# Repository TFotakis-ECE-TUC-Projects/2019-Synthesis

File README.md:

# TUC Course: Analysis and Design (Synthesis) of Telecommunication Systems
## Project: Distributed Smoke Detection using Lasers

### Development Team Members
Andrianakis Manos
Fotakis Tzanis
Giannakopoulos Orestis
Kotridis Giorgos
Neonakis Paulos
Nichoritis Thanos
Ouroutzoglou Michail
Piskopos Dionisis
Polyzos Christos
Topalis Thanasis

### Professor Assistants
Giannelos Vaggelis
Vougioukas Giorgos

## Supervisor Professor
Bletsas Aggelos

# Introduction
---

## Semester Project Overview
The purpose of this project is to create a wireless sensor network in order to detect smoke in the TUC ECE's department building canteen and pinpoint its source.

### Main idea
Smoke has the ability to diffuse and absorb light, thus, by utilizing cheap sensors such as photodiodes, phototransistors or even photovoltaic panels, the impinging light’s intensity can be tracked and from its waveform in respect to time the existence of smoke can be inferred.
In order to cover a large amount of the available plane, lasers can be used in combination with mirrors as shown in Fig.1. By dividing the plane into cells/tables of 2 rows and 3 columns (see Fig.1), detection of smoke in a specific cell/table can be done by combining data from multiple sensors (e.g., row-1 and column-2 could detect smoke from table-2). 

### Project Structure
Work was split into 3 working groups, Hardware, Middleware and Software, in order to divide the workload among the project members. 
The system includes five sensor nodes (slaves, depicted in Fig.2-right), one base node (master, depicted in Fig.3) and one server PC (laptop, depicted in Fig.4). 
    • Slave: Controls laser diode, measures laser intensity and sends the measurement to the master node.
    • Master: Gives instructions to slave nodes so that they get synchronized to make the laser intensity measurements and to report them back on specific time slots. After the collection of all the measurements, a message to the server is sent with the collected data.
    • Server: Collects measured data, runs the detection algorithm on the collected data and updates the website.

Figure 1: Initial idea. Top view.

Figure 2: Slave Node on the left, mirror on the right.

Figure 3: Master Node.

Figure 4: Server on a laptop on the left, Server on a Raspberry Pi Zero W on the right.

Figure 5: Fully connected System.

### Technical Difficulties
Due to environmental difficulties (walls prone to machinery vibrations, mounting issues, etc) that will be discussed below, time limitations became significant to the project’s overall development. As a result, the initial goal of detecting smoke on a grid was transformed into detecting smoke on a serial basis.

# Implementation
---

## Hardware

In this section we shall describe the analog part of our system. 

First of all, we shall analyze the basic hardware, as well as the installation components, that compose the system’s slave nodes.
Components:
    • Diode Laser (red)
    • Photovoltaic Panel
    • Power Supply
    • Mirror reflectors
    • Switching circuit
    • Optical filter
    • Control Unit & Radio
    • Case
    • Mounting Materials

### Diode Laser
For the purpose of our project, Diode Lasers (red) were the most power efficient and low cost. Additionally, red light has the biggest wavelength (compared with green and blue) thus, it is the least harmful for the human eye.

### Photovoltaic Panel
The photovoltaic panel is connected to the ADC (Analog to Digital Converter) of the Daughter Card in order to digitalize the signal.
Power Supply
The power supply was a major and very challenging problem we had to solve. Our first approach was to use conventional batteries. However, this approach did not provide a strictly constant DC voltage as long as the batteries were quickly discharged. So we had to make a regulator circuit to overcome this problem. Instead of this we used power banks, which were low cost, efficient, rechargeable and provided the desired DC constant power supply.
Mirror reflectors
Used to redirect the light beam to the desired destination.

### Switching Circuit

Figure 6: Laser amplifier circuit.

This circuit was used for duty-cycle purposes, in the interest of minimizing the power consumption of the project. For the implementation of the switching circuit we used the following components:
    • 10 kΩ resistance
    • 2N3904 transistor
The switch circuit is represented in Fig. 6. In order to use the transistor as a switch circuit, we connected a 3,3 V output provided by the used target board via a resistance to the Base of the transistor, while connecting the output of the transistor (Collector) to the negative polarity of the diode laser. As a result, we manage a power consumption approximately to 100 mW for each laser circuit contained in a grid.

### Optical filter
In order to eliminate the ambient light’s intensity inside the slave’s case and only let the laser pass through, optical filters were used. An optical filter is a semi-transparent material that absorbs specific light wavelengths. The ones used in this project were filters that only allowed red pass through, which is the color of the used lasers. Such a filter could be purchased as a sheet of paper. However, for the purposes of this project and because of time shortage, several layers of red colored transparent tape were used in the place of the optical filter. Although, an optical filter cannot cut off the whole ambient light (ambient light also includes red wavelengths) and at the same time let the red laser pass through, it was a good enough solution, cutting off most of the other wavelengths.

### Control Unit & Radio
The slave node’s Control Unit & Radio is comprised of a Silicon Labs C8051F321 Daughter-Card, an 8-bit microcontroller mounted on a small development board with various IO ports (Buttons, IO pins, MicroUSB connector, etc), and a Silicon Labs CC2500 Radio Shield, which is an 8-bit microcontroller with radio modulation capabilities and I2C communication. It is responsible for collecting the needed measurements through its ADC (Analog to Digital Converter) component (see Middleware section), processing them and sending them to the master node and, also, switching its laser’s state for maintaining the system’s low power consumption characteristics.

### Case
Second handed Electrical Junction Boxes were used to accommodate all slave’s components. Two holes were drilled on its front face, one for holding the laser diode and one for letting the laser beam enter the box and hit the photovoltaic panel. The photovoltaic panel was placed as far from the hole as possible in order to eliminate the ambient light hitting it for reasons that will be discussed in the middleware section. For further elimination, the aforementioned optical filter was placed on top of that hole.

### Mounting Materials
Mounting hardware not only inside the slave’s case but also on the walls without establishing permanent installations (e.g. using holes and/or screws) that could damage the building, was a difficult, time and resource consuming task. Solutions such as 3D printed bases were tested in combination with materials such as Blu Tack and double sided tapes. Despite their light weight, stability problems surfaced. Therefore, the lasers' beams were diverted from the target. At last, the slaves cases were mounted on the walls using double sided tape and the reflection mirrors using only Blu Tack, which helped to easily redirect the laser beams.

### Slave Node Overview
Fig. 7 shows the wiring between the components we already discussed. Concerning the power supply of the circuit we used the daughter-card’s pins to provide power for both the circuit and the positive polarity of the laser diode. The daughter-card feeds the laser positive polarity and the switching circuit’s enable signal with VCC = 3.3V. Finally, the daughter-card’s power was provided by a 5V, 2600 mAh power bank which, in paper, could last for more than 18-hours of continuous use.

Figure 7: Inside a slave’s casing.

### Master Node Overview
The base station/master node is comprised of a Silicon Labs C8051F320 DevKit, an 8-bit microcontroller mounted on a development board with various IO ports (Buttons, IO pins, DB9 connector, power supply connector, etc), a Silicon Labs CC2500 Radio Shield, an 8-bit microcontroller with radio modulation capabilities and I2C communication, a 5V power adapter and a Serial to USB adapter. The master node exchanges data with all slave nodes via the aforementioned radio shield. The collected data is then forwarded to the server via the DevKit’s serial port (utilizing its UART capabilities), which is then adapted to a USB port through the Serial to USB adapter. The latter is needed because, at the time of writing this report, the serial port is being deprecated and obsolete from every modern PC and also the Laptop/Raspberry Pi was used as a server.

## Middleware

### Connecting The Devices
The main objective was to collect the voltage values from each of the five slaves to the master node in order to forward them to the software to be processed for the detection. Achieving a reliable communication between one slave and the master was the first aim. Afterwards, the master node’s code was adjusted in order to control the rest.
The implementation began by writing code for the exchange of simple packets between the master and the slaves. RF-related registers were fine-tuned with the aid of the smartRF studio 7, which is an application that takes as input the desired design parameters and returns code that configures the nodes’ radios accordingly.
Every device can be used in one of the two available modes, receiver mode and transmitter mode, at a time. Checking for good communication between devices, one was set in transmitter mode and the other in receiver mode. As soon as they exchanged a single packet they would both switch modes and begin a new packet exchange. This process of exchanging packets would continue until a packet was lost. This method is called ping pong because a single packet is sent from one device to another and back again, like a ball of ping pong. 

### Handling the Data
After a reliable communication between devices has been established, the next step was to measure voltage values given from a power supply using the daughter-card’s analog-in pins and converting them into bytes, which will be later sent to the master. For this procedure an ADC (analog to digital converter) is required, an electronic component inside the slave’s microcontroller, which by comparing a port’s voltage to a set reference voltage, returns a measurement from 0 to 1023 of how close the port’s voltage is to the reference’s voltage. This method is called analog to digital conversion, because it accepts an analog, continuous signal and converts it into a discrete number referring to a specific moment of time. Following the addition of the appropriate functionality for the ADC part, the results of the converter were put in the tx Buffer (the buffer where the values that we want to be sent are into) in order to be transmitted to the master. After receiving the values from the slave, it was needed to view if the values from the power supply were sent correctly and in order to the master. Functionality extension had be made on the master, so that serial port communication capabilities could be used via the UART protocol. In order to view the received data from the PC, the Hercules application was used.

### Communication protocol
According to the initial plan, the master node was supposed to send a request to the first slave, waiting to receive a measurement, and then proceed to the next. After the implementation of this protocol, we came to the conclusion that this was not the ideal method as the whole procedure took around 2.5 seconds (500ms for each slave). This period was way too big for a smoke detection task, so a new, faster protocol had to be designed.
The final communication protocol expects the master to broadcast to all slaves an instruction to take a measurement. After the needed period of time for a measurement to be made (approximately 200ms), the master, starting from the first slave, sends a packet to request for that measurement and when received it continues to the next one, until it has collected all slaves’ measurements. That method was proved to be fast enough for our implementation as the elapsed time is being reduced to around 500ms.
Although, another issue occurred, as in unpredicted time, the communication ended suddenly, because a transmitted packet was lost. In this case, the procedure crashed as the master waited forever for a packet to be received. For that reason, a timeout routine was created which leads to a timeout after a short, pre defined period of time of 100ms, in order to avoid system crashes. When a timeout occurs, master continues its execution and requests the next node’s measurement. As a result, even in the case that a slave node is being lost from the network (e.g. battery fully discharged, change in environment leading to poor network connection, etc), the system’s execution will continue with no impact, except for always sending the last received measurement of the lost node.

### Measurements
To get a sense of the photovoltaic’s behaviour under the ambient light and the selected laser beam, measurements were made using one of the lab’s oscilloscope. Because most of the ambient light was generated from fluorescent lamps, which their operating principle is charging mercury to emit ultraviolet light to the tube’s gas, which it then emits visible light, a frequency of around 100 Hz was detected. Trying to remove that frequency, as well as, the ADC’s measurement noise, an average of 2048 measurements was computed, which was then sent to the master.
As soon as the first real world test took place at the desired area revealing the realistic measurements that had to be taken under consideration, a slight change in the measurement’s functionality had to be made in order to increase the sensitivity. The previous measurement method disadvantage was that it only measured ambient light’s intensity (which cannot be avoided) in combination with the laser’s intensity. However, the wanted measurement was (if possible) to measure only the laser’s intensity. So, to eliminate the ambient light’s intensity, it had to be measured and subtracted from the combination of ambient light and laser. The final measurement method works as follows: 
The laser is turned on, while the ADC takes 1024 measurements which are summed up to a variable, SUM, representing a measurement of the combination of the ambient light and the laser. Afterwards, the laser is turned off, while the ADC takes another 1024 measurements, which represent a measurement of the current ambient light. Those measurements are then subtracted from the SUM variable. Finally, the SUM is divided by 1024 to calculate the measurements’ arithmetic mean, which represent a close approximation of the laser’s intensity. To further eliminate ambient light’s intensity which caused the photovoltaic to operate on its nonlinear area, an optical filter, which only lets red (the laser’s color) to pass through, was used as discussed above.

### Master Node Algorithm Flow Chart

Figure 8

### Slave Node Algorithm Flow Chart

Figure 9

## Software
The software team was responsible for fetching the data from the master node, keeping a log of them, and plotting them on MATLAB-like environment for the user to overwatch. In addition to that, accurate real-time detection of smoke is offered through simple digital signal processing, as well as the ability to project this information on a website, reachable from throughout the campus, alongside (un)pleasant sound effects as a notification/warning for the end user.

### Website & Data Handling
The website’s backend was created using the DJango framework, a high level web framework for rapid development, clean and pragmatic design. As it uses Python, it was the most suitable for the project’s needs because the smoke detection algorithm could be easily implemented inside the backend’s features. Last but not least, the data collection from the master node is done using the UART protocol through the PC’s serial port. 
On server launch, a new thread is created with the purpose of reading the serial port and storing its data into a FIFO buffer, from which the detection algorithm could make the needed calculations. Whenever a new calculation is ready, it is stored in a variable which can be sent to all the website’s connected clients. This thread also logs the received data, the timestamp of each measurement and the result of the detection. This can be quite useful since it allows the user to examine events in the past, even if the system is left unsupervised.
Another thread is also spawned in order to plot the received waveforms of each sensor on the screen.
The reason why separate threads are needed is because some of the aforementioned functionalities are blocking, meaning that the server would not continue its execution if single threaded.
The website’s frontend was created using plain HTML5 and CSS3 for the user interface as well as jQuery for dynamically updating the states of the predefined measured areas. In more detail, when the website is accessed, a periodic routine is triggered every 8 second to request from the server the current areas’ states. A json response is returned from the backend containing the needed data, which are stored in the previously mentioned variable. 
Whenever smoke is detected in an area, the corresponding area on the website turns from green to red and a sound effect is played, in order to catch the attention of the users.

### Observations On Data
Several factors were considered before deciding what is a good way to approach the detection. 
The ambient light introduced bias on the sensors. Normally this wouldn’t pose a problem, however considering the day/night cycle as well as the lights turning on/off, this was a problem. In addition to that, if the smoke settled in the room, the ambient light as well as the laser rays would be affected by a slow, time-dependant factor (e.g., day/night transition, smoke clearing out). These effects are different on each sensor considering their different location in the room and their electronic characteristics (e.g., panels are physically very different from each other).
The above observations are proof that the detection method needs to be able to adjust on its own, for each sensor, to a slow changing environment.
In contrast to the previous, instability on the part of the mirrors, due to vibrations etc., coupled with the thermal noise of the ADC, flickering can be noticed on the measurements. This small fluctuation needs to be filtered out and not be considered in the detection as it can potentially cause false positives.
Thus, it is now clear that the constant (or very slow), and fast components of the received waveforms must be discarded.

### DSP & Detection
Having said that, the digital signal processing part is now a lot more straightforward. By performing Discrete Time Fourier Transform (DTFT) on small time frames of the received waveforms, frequencies (such as the above) can be cropped in order to detect smoke from the rest of the signal. When there is no smoke, the intermediate frequencies (higher than 0 less than 1, see Fig. 11 left) offer small contribution to the overall signal. However, when smoke passes through the laser ray, a sudden drop at the sensor level occurs (also see in Fig. 11 right, how the intermediate frequencies get significant amplitude). A heuristic metric was developed by calculating the arithmetic mean of the absolute value of the intermediate frequencies. Through trial and error, a heuristic threshold value was identified and used as a means of checking whether there is smoke or not. Surprisingly, this method works quite good, all things considered.

Figure 10: Real-time monitoring of Sensor Level.

Figure 11: The top figures are time windows without and with smoke. The bottom figures are their corresponding FFT waveforms. 

Figure 12: Waveform of sensor level (top), alongside the FFT based metric compared to the heuristic threshold (bottom). 

Figure 13: Website view without smoke.

Figure 14: Website view with smoke.

# Future Work
---
## Hardware
Low cost laser modules come with low quality, poor focus performance and endurance. In addition, generic mirrors affects laser beams’ focus and intensity over multiple reflections. Overall, the received beam on the photovoltaic panel loses its property of being a “beam” as it is getting distorted after all the needed reflections and its initial low focus. Optimizing the laser’s wavelength by selecting the one that gets the greatest absorption from gases that need to be detected, even other than smoke or even invisible to the human eye such as CO or dangerous flammable gases. Furthermore, optimized optical filters, better mounting solutions and smaller casing could improve sensitivity and ease of installation. 

## Middleware
Power consumption can be reduced using the minimum required  power output of transmitter in order to meet the requirements of  sensitivity of receiver for a successful communication. Also, lower data rate could lead to power efficiency.

## Software
Due to time constraints, the detection had to be performed in a simple straightforward way. The result is that we came up with a heuristic metric and a heuristic threshold that may require fine-tuning overtime. In the future, neural networks could be facilitated in order to make the system smarter and enabling it to pinpoint the exact location of the smoke, by comparing values of multiple (with possibly intersecting rays) sensors. Another benefit of this approach would be that we can drop the heuristic metrics and thresholds, thus making the detector much more robust and independent (in terms of fine-tuning).

# Links
---
Youtube Demo Video: https://youtu.be/7rDN7ZuSLMw
GitHub Repository: https://github.com/TFotakis/TUC-Synthesis

# The Team
---

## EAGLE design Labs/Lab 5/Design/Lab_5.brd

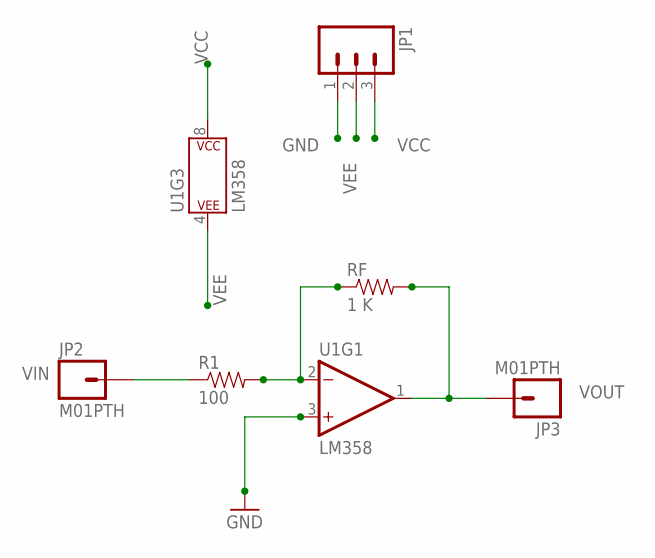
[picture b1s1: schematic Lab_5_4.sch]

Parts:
JP1: M03LOCK; 1X03_LOCK
JP2, JP3: M01PTH; 1X01
R1: 100; 1206
RF: 1 K; 1206
U1: LM358; DIP08-KIT

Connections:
FDBCK: R1.2, RF.1, U1.2 (-IN)
GND: JP1.1, U1.3 (+IN)
VCC: JP1.3, U1.8 (P$V+)
VEE: JP1.2, U1.4 (P$V-)
VIN: JP2.1, R1.1
VOUT: JP3.1, RF.2, U1.1 (OUT)

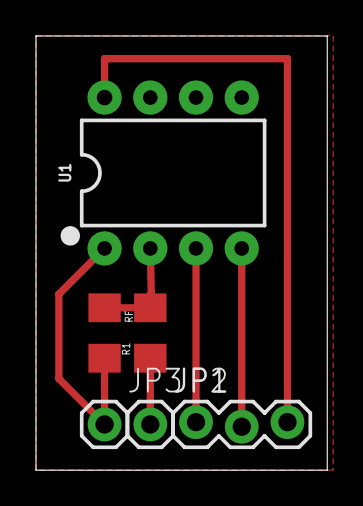
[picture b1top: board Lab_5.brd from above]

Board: 2 copper layers, 16.2 x 24.1 mm, 6 parts (0 on the bottom side), 6 nets.

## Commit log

2018-12-07 Implemented Server UI
2018-12-07 Updated Allowed hosts
2018-12-15 Updated Readme - Uploaded Network Top View - Reconstructed Middleware master & slave
2018-12-15 Updated Readme - Uploaded NetworkTopView.png
2018-12-17 Changed master printf message & led - Changed slave led & send data - Updated detection.py
2018-12-18 Updated detection.py - Cleaned up slave.c - First implementation of PWM on CEX0 on master (On/Off Using UART Pending)
2018-12-20 Implemented UART0 Interrupt on master
2019-01-14 Changed middleware protocol - Broadcast a 'Measure' message and then unicast a 'Send measurement' Message
2019-01-17 Switched rfSettings to Max Gain and lowest bit rate
2019-01-17 Some measurements and modifications on the detection code.
2019-01-17 Implementer DROP_AMBIENT_LIGHT on slaves
2019-01-17 amazing changes. added plotter. other small changes to detection.
2019-01-17 added fire alert
2019-01-17 Trying to implement WDT on master
2019-01-18 Implemented master transmitting on channel 0 and receiving on channel 1
2019-01-18 Implemented Timeout on master rxMode
2019-01-30 finalised detection. pushing changes and all log data
2019-01-30 Software: import pynput iff TRAINING is true (do not import when running on RPi)
2019-02-12 Updated README.md Texts
2019-02-12 Inserted images on README.md

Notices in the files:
parts and their libraries:
SparkFun: Licensing: CC v3.0 Share-Alike You are welcome to use this library for commercial purposes.
SparkFun-IC-Amplifiers: Licensing: Creative Commons ShareAlike 4.0 International - https://creativecommons.org/licenses/by-sa/4.0
